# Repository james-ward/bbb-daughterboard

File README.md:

# bbb-daughterboard
Files for a PCB that plugs into a BeagleBone Black and provides easy access to PWM ports and QEP ports. Includes an MPU6050 IMU chip.

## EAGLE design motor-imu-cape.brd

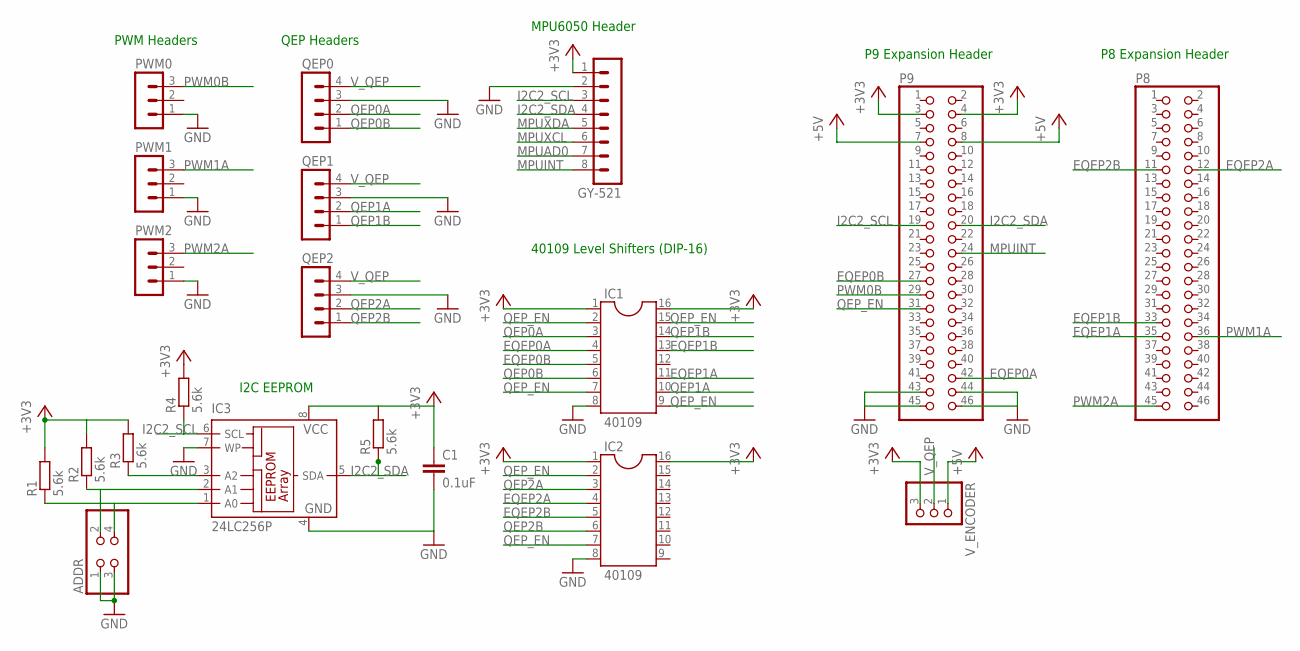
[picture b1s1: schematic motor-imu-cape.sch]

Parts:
ADDR: PINHD-2X2; 2X02
C1: 0.1uF; C025-024X044
GY-521: MA08-1
IC1, IC2: 40109; DIL16
IC3: 24LC256P; DIL8
P8, P9: PINHD-2X23; 2X23
PWM0, PWM1, PWM2: MA03-1
QEP0, QEP1, QEP2: MA04-1
R1, R2, R3, R4, R5: 5.6k; 0204/7
V_ENCODER: PINHD-1X3; 1X03

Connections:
+3V3: C1.1, GY-521.1, IC1.1, IC1.16, IC2.1, IC2.16, IC3.8 (VCC), P9.3, P9.4, R1.2, R2.2, R3.2, R4.2, R5.2, V_ENCODER.3
+5V: P9.7, P9.8, V_ENCODER.1
EQEP0A: IC1.4, P9.42
EQEP0B: IC1.5, P9.27
EQEP1A: IC1.11, P8.35
EQEP1B: IC1.13, P8.33
EQEP2A: IC2.4, P8.12
EQEP2B: IC2.5, P8.11
GND: ADDR.1, ADDR.3, C1.2, GY-521.2, IC1.8, IC2.8, IC3.4 (GND), IC3.7 (WP), P9.43, P9.44, P9.45, P9.46, PWM0.1, PWM1.1, PWM2.1, QEP0.3, QEP1.3, QEP2.3
I2C2_SCL: GY-521.3, IC3.6 (SCL), P9.19, R4.1
I2C2_SDA: GY-521.4, IC3.5 (SDA), P9.20, R5.1
MPUAD0: GY-521.7
MPUINT: GY-521.8, P9.24
MPUXCL: GY-521.6
MPUXDA: GY-521.5
unnamed: IC3.3 (A2), R3.1
unnamed: ADDR.2, IC3.2 (A1), R2.1
unnamed: ADDR.4, IC3.1 (A0), R1.1
PWM0B: P9.29, PWM0.3
PWM1A: P8.36, PWM1.3
PWM2A: P8.45, PWM2.3
QEP0A: IC1.3, QEP0.2
QEP0B: IC1.6, QEP0.1
QEP1A: IC1.10, QEP1.2
QEP1B: IC1.14, QEP1.1
QEP2A: IC2.3, QEP2.2
QEP2B: IC2.6, QEP2.1
QEP_EN: IC1.2, IC1.7, IC1.9, IC1.15, IC2.2, IC2.7, P9.31
V_QEP: QEP0.4, QEP1.4, QEP2.4, V_ENCODER.2

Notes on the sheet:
P9 Expansion Header
P8 Expansion Header
MPU6050 Header
PWM Headers
QEP Headers
40109 Level Shifters (DIP-16)
I2C EEPROM

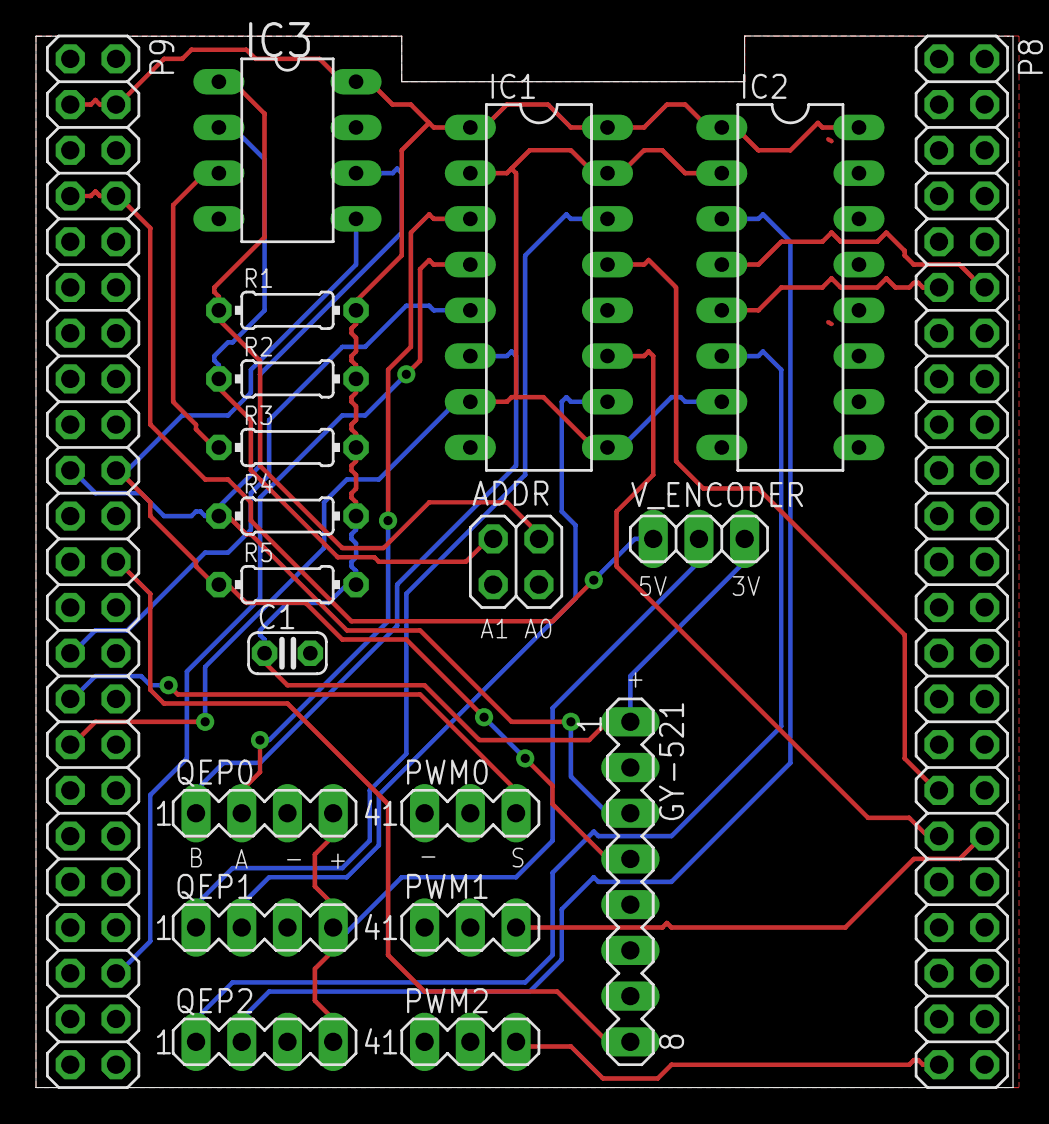
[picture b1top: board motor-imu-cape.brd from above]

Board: 2 copper layers, 54.3 x 58.4 mm, 20 parts (0 on the bottom side), 26 nets.

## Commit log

2015-07-07 Invensense MPU library
2015-07-08 Create project and remove library
2015-07-08 Create BBB headers
2015-07-08 Label ports on Cape Expansion ready for wiring
2015-07-09 Add pin holes for MPU6050
2015-07-09 Add 40109 and it's library and wire up its ports for one qep
2015-07-09 Have only one ground and create second 40109
2015-07-09 Put in qepenables
2015-07-10 Replace 40109s with dip 16s
2015-07-10 PWM and QEP headers added
2015-07-10 Add qepenable to cape
2015-07-14 Cleanup files to stop tracking previous revisions.
2015-07-14 Replace P8 and P9 with single, custom pin headers. Minor cleanups.
2015-07-14 Insert EEPROM and encoder voltage jumpers.
2015-07-14 Layout: set board dimensions and place P8 and P9.
2015-07-14 Cleanup and rename files.
2015-07-15 Board WIP
2015-07-16 Don't track layout attempts.
2015-07-16 Fix issues with ground planes.
2015-07-17 Overlay for pin enabling.
2015-07-23 Labels and logo
2015-07-23 Label jumpers
2015-07-23 Final label adjustment.
2015-07-23 Reshuffle labels
2015-07-23 Change qep voltage jumper labels
2015-07-23 Autoroute traces and get ready for logo
2015-07-24 Final layout changes for submission to oshpark for fab.
